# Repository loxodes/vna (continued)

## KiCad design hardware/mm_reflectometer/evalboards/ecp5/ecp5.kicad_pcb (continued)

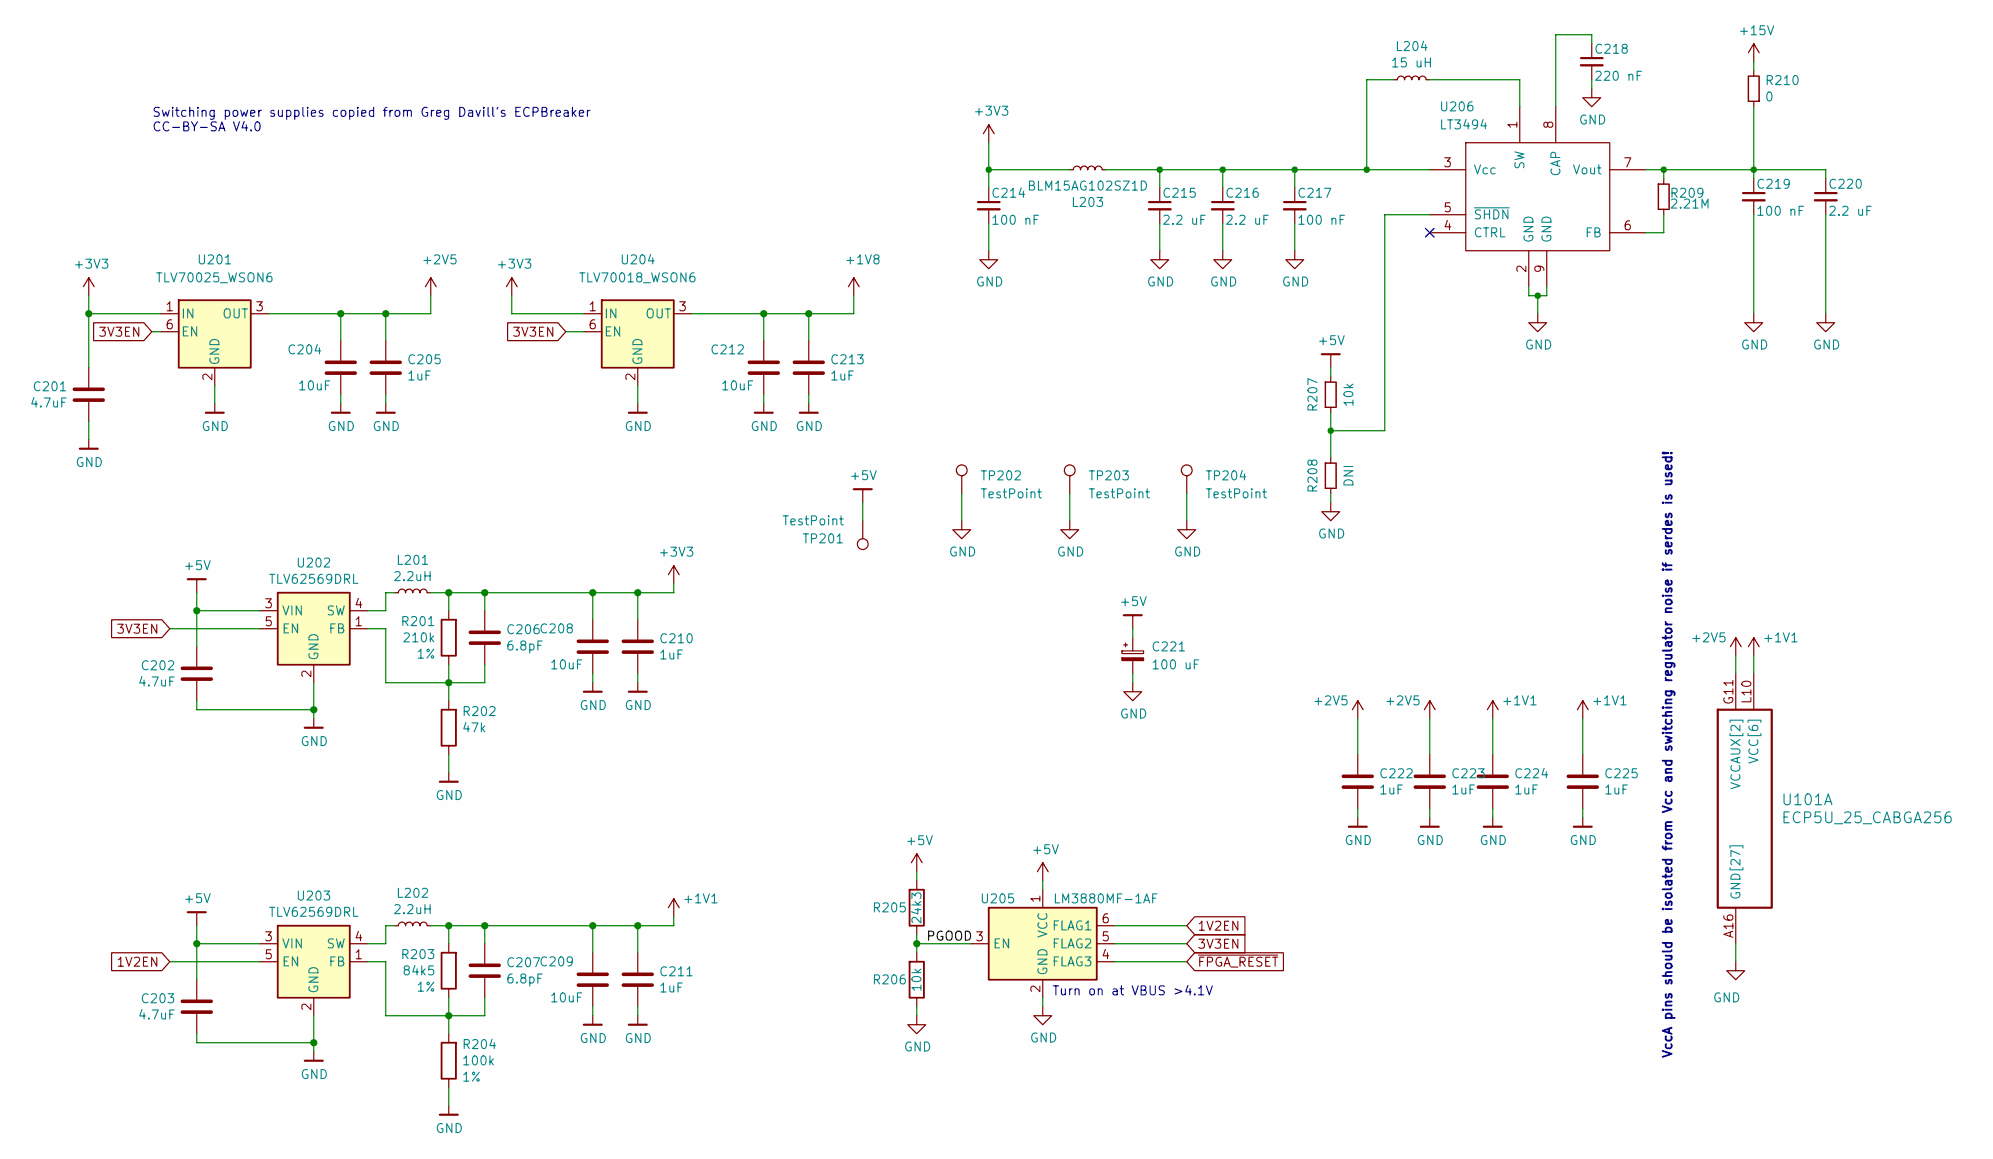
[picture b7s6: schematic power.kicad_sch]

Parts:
C201, C202, C203: 4.7uF; C_0402_1005Metric
C204, C208, C209, C212: 10uF; C_0603_1608Metric
C205, C210, C211, C213, C222, C223, C224, C225: 1uF; C_0402_1005Metric
C206, C207: 6.8pF; C_0402_1005Metric
C214, C217: 100 nF; C_0402_1005Metric
C215, C216, C220: 2.2 uF; C_0603_1608Metric
C218: 220 nF; C_0603_1608Metric
C219: 100 nF; C_0603_1608Metric
C221: 100 uF; CP_Elec_6.3x5.8
L201, L202: 2.2uH; L_0805_2012Metric
L203: BLM15AG102SZ1D; L_0402_1005Metric
L204: 15 uH; L_1210_3225Metric
R201: 210k; R_0402_1005Metric
R202: 47k; R_0402_1005Metric
R203: 84k5; R_0402_1005Metric
R204: 100k; R_0402_1005Metric
R205: 24k3; R_0402_1005Metric; MPN RC0402FR-1324K3L
R206: 10k; R_0402_1005Metric; MPN RC0402FR-1310KL
R207: 10k; R_0402_1005Metric
R208: DNI; R_0402_1005Metric
R209: 2.21M; R_0402_1005Metric
R210: 0; R_0603_1608Metric
TP201, TP202, TP203, TP204: TestPoint; TestPoint_Keystone_5015_Micro-Minature
U101: ECP5U_25_CABGA256; BGA-256_14.0x14.0mm_Layout16x16_P0.8mm_Ball0.45mm_Pad0.32mm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
U201: TLV70025_WSON6; WSON-6_1.5x1.5mm_P0.5mm
U202, U203: TLV62569DRL; SOT-666
U204: TLV70018_WSON6; WSON-6_1.5x1.5mm_P0.5mm
U205: LM3880MF-1AF; SOT-23-6; MPN LM3880MFX-1AF/NOPB
U206: LT3494; DFN-8-1EP_2x3mm_P0.5mm_EP0.61x2.2mm

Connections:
1V2EN: U203.5 (EN), U205.6 (FLAG1)
3V3EN: U201.6 (EN), U202.5 (EN), U204.6 (EN), U205.5 (FLAG2)
+1V1: C207.1, C209.1, C211.1, C224.1, C225.1, L202.2, R203.2, U101.G6 (VCC[6]), U101.G7 (VCC[6]), U101.G9 (VCC[6]), U101.L8 (VCC[6]), U101.L9 (VCC[6]), U101.L10 (VCC[6])
+1V8: C212.1, C213.1, U204.3 (OUT); also elsewhere on the board
+2V5: C204.1, C205.1, C222.1, C223.1, U101.G11 (VCCAUX[2]), U101.L7 (VCCAUX[2]), U201.3 (OUT)
+5V: C202.1, C203.1, C221.1, R205.2, R207.1, TP201.1, U202.3 (VIN), U203.3 (VIN), U205.1 (VCC); also elsewhere on the board
+15V: R210.2; also elsewhere on the board
/power/PGOOD: R205.1, R206.2, U205.3 (EN)
GND: C201.2, C202.2, C203.2, C204.2, C205.2, C208.2, C209.2, C210.2, C211.2, C212.2, C213.2, C214.2, C215.2, C216.2, C217.2, C218.2, C219.2, C220.2, C221.2, C222.2, C223.2, C224.2, C225.2, R202.1, R204.1, R206.1, R208.2, TP202.1, TP203.1, TP204.1, U101.A1 (GND[27]), U101.A16 (GND[27]), U101.D2 (GND[27]), U101.D15 (GND[27]), U101.F8 (GND[27]), U101.F9 (GND[27]), U101.G8 (GND[27]), U101.G10 (GND[27]), U101.H1 (GND[27]), U101.H8 (GND[27]), U101.H9 (GND[27]), U101.H10 (GND[27]), U101.H16 (GND[27]), U101.J8 (GND[27]), U101.J9 (GND[27]), U101.J10 (GND[27]), U101.K6 (GND[27]), U101.K7 (GND[27]), U101.K8 (GND[27]), U101.K9 (GND[27]), U101.K10 (GND[27]), U101.N2 (GND[27]), U101.N15 (GND[27]), U101.T1 (GND[27]), U101.T5 (GND[27]), U101.T12 (GND[27]), U101.T16 (GND[27]), U201.2 (GND), U202.2 (GND), U203.2 (GND), U204.2 (GND), U205.2 (GND), U206.2 (GND), U206.9 (GND); also elsewhere on the board
unnamed: C206.2, R201.1, R202.2, U202.1 (FB)
unnamed: C207.2, R203.1, R204.2, U203.1 (FB)
unnamed: C215.1, C216.1, C217.1, L203.1, L204.1, U206.3 (Vcc)
unnamed: C218.1, U206.8 (CAP)
unnamed: C219.1, C220.1, R209.1, R210.1, U206.7 (Vout)
unnamed: L201.1, U202.4 (SW)
unnamed: L202.1, U203.4 (SW)
unnamed: L204.2, U206.1 (SW)
unnamed: R207.2, R208.1, U206.5 (~SHDN)
unnamed: R209.2, U206.6 (FB)
~FPGA_RESET: U205.4 (FLAG3); also elsewhere on the board

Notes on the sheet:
Switching power supplies copied from Greg Davill's ECPBreaker CC-BY-SA V4.0
Turn on at VBUS >4.1V
VccA pins should be isolated from Vcc and switching regulator noise if serdes is used!

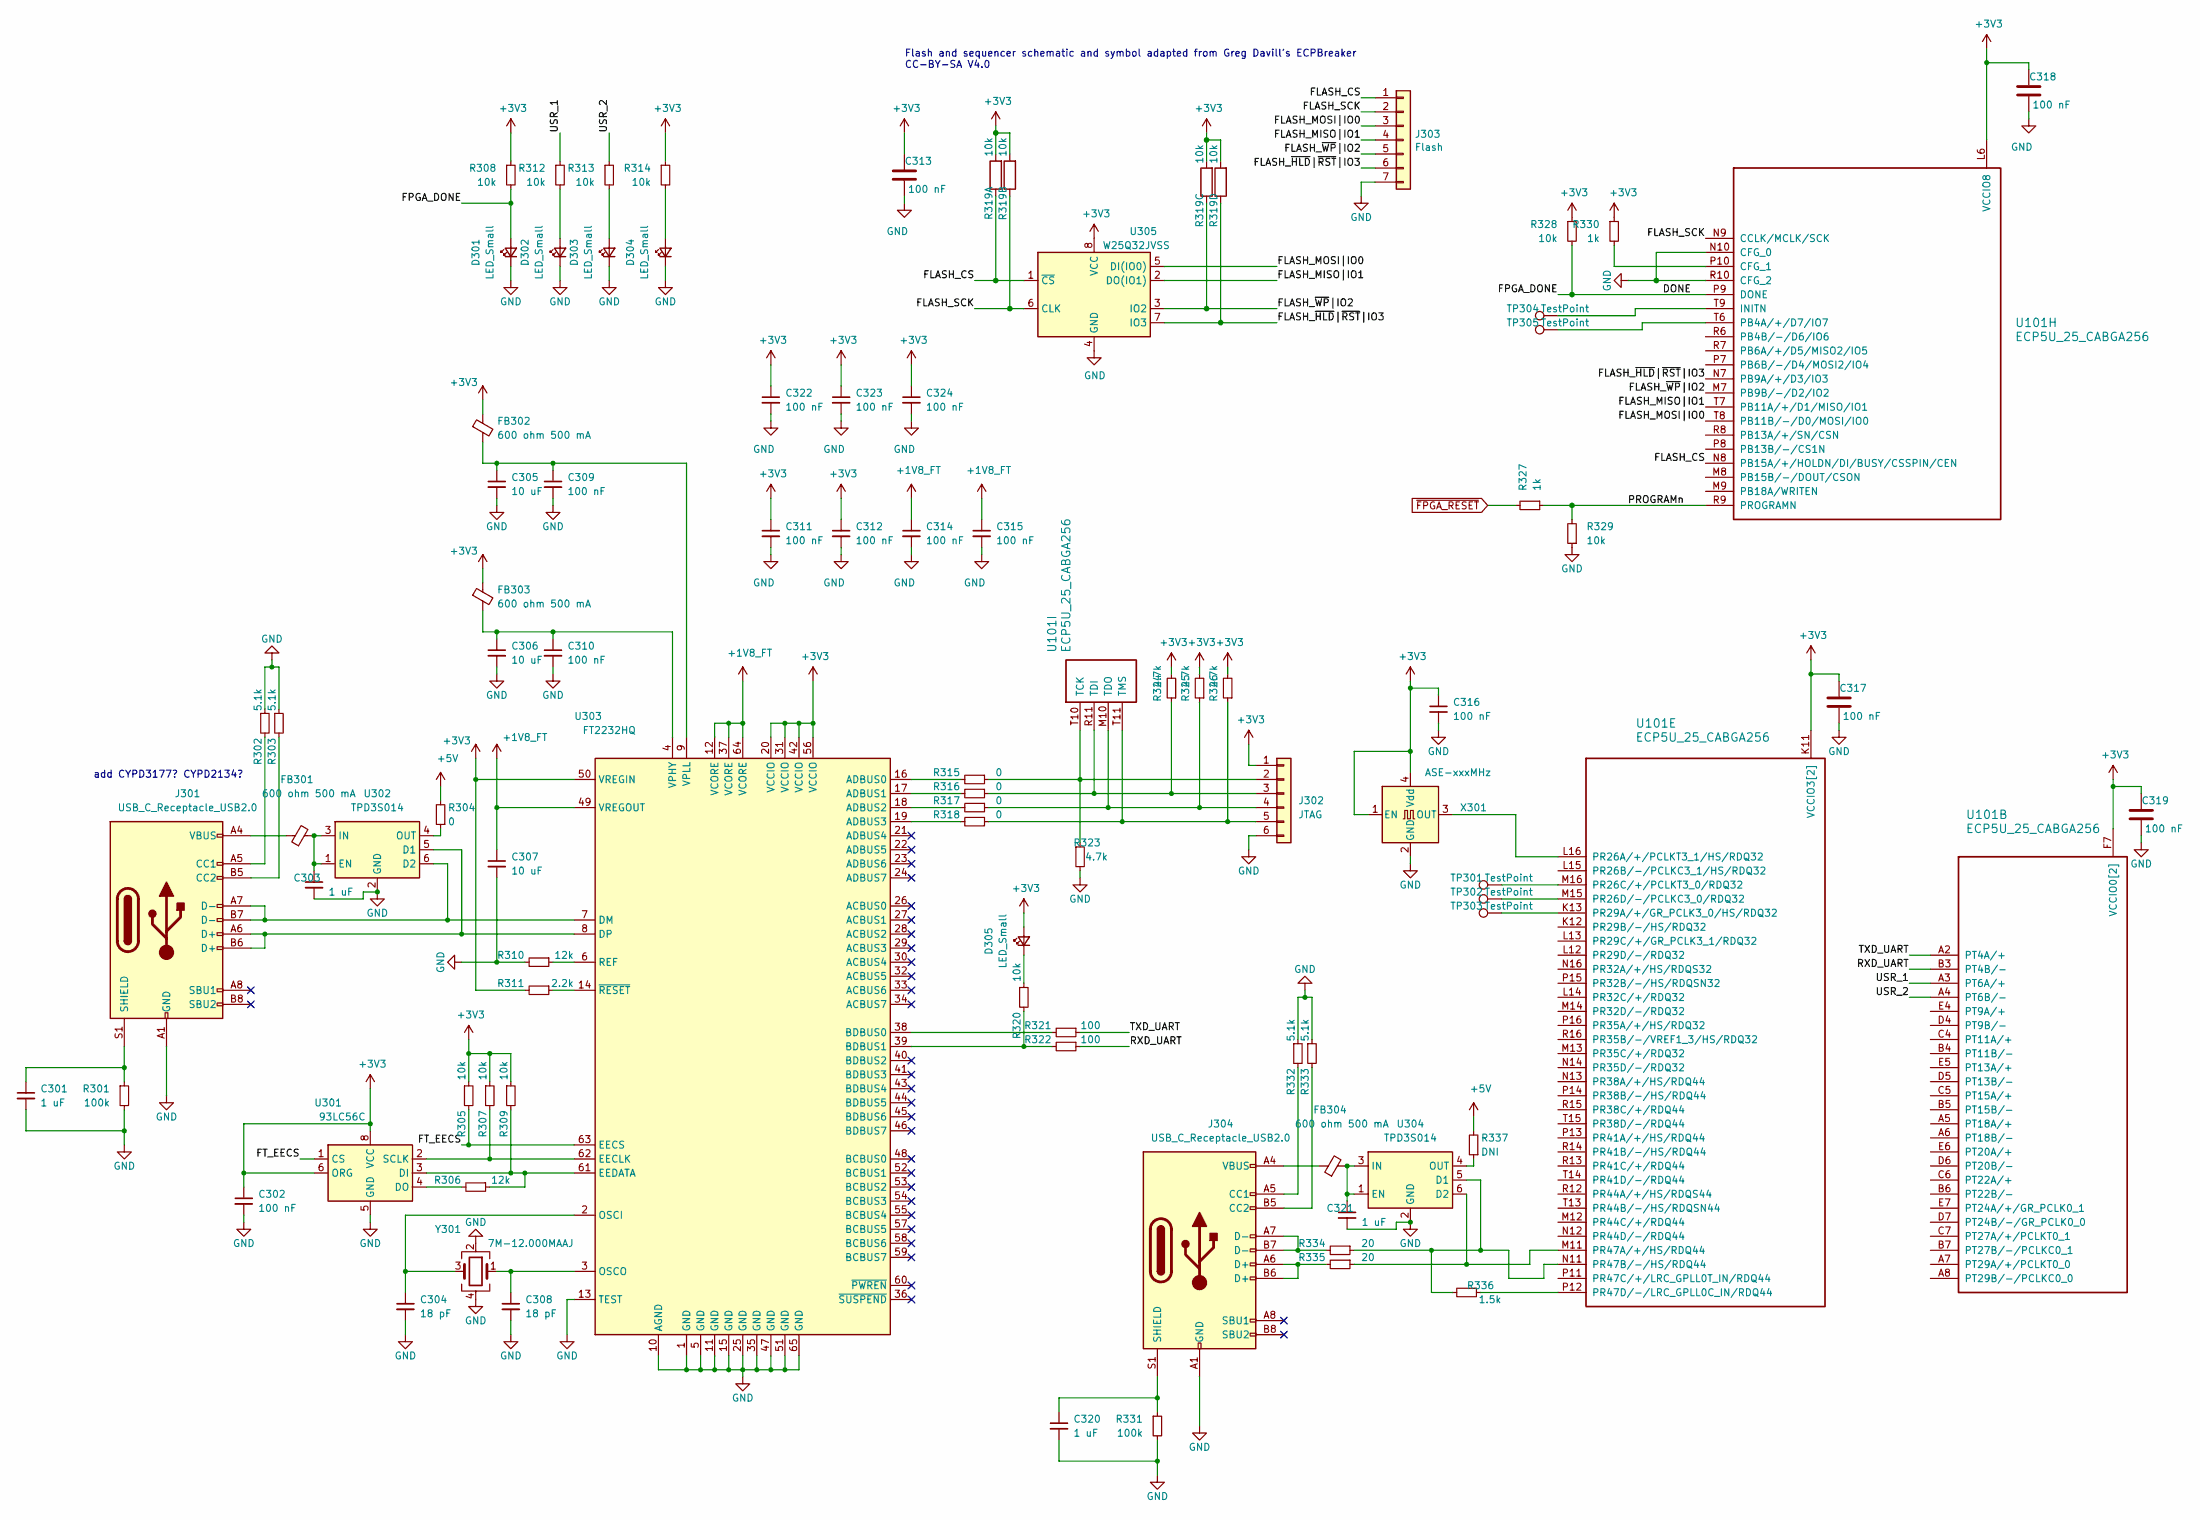
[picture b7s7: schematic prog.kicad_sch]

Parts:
C301, C303, C320, C321: 1 uF; C_0402_1005Metric
C302, C309, C310, C311, C312, C313, C314, C315, C316, C317, C318, C319, C322, C323, C324: 100 nF; C_0402_1005Metric
C304, C308: 18 pF; C_0402_1005Metric
C305, C306, C307: 10 uF; C_0603_1608Metric
D301, D302, D303, D304, D305: LED_Small; LED_0603_1608Metric
FB301, FB302, FB303, FB304: 600 ohm 500 mA; L_0603_1608Metric
J301, J304: USB_C_Receptacle_USB2.0; USB_C_Receptacle_HRO_TYPE-C-31-M-12
J302: JTAG; PinHeader_1x06_P2.54mm_Vertical
J303: Flash; PinHeader_1x07_P2.54mm_Vertical
R301, R331: 100k; R_0402_1005Metric
R302, R303, R332, R333: 5.1k; R_0402_1005Metric
R304, R315, R316, R317, R318: 0; R_0402_1005Metric
R305, R307, R308, R309, R312, R313, R314, R320, R328, R329: 10k; R_0402_1005Metric
R306, R310: 12k; R_0402_1005Metric
R311: 2.2k; R_0402_1005Metric
R319: 10k; R_Array_Convex_4x0402
R321, R322: 100; R_0402_1005Metric
R323, R324, R325, R326: 4.7k; R_0402_1005Metric
R327, R330: 1k; R_0402_1005Metric
R334, R335: 20; R_0402_1005Metric
R336: 1.5k; R_0402_1005Metric
R337: DNI; R_0402_1005Metric
TP301, TP302, TP303, TP304, TP305: TestPoint; TestPoint_Pad_D1.5mm
U101: ECP5U_25_CABGA256; BGA-256_14.0x14.0mm_Layout16x16_P0.8mm_Ball0.45mm_Pad0.32mm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
U301: 93LC56C; SOIC-8_5.23x5.23mm_P1.27mm
U302, U304: TPD3S014; SOT-23-6
U303: FT2232HQ; QFN-64-1EP_9x9mm_P0.5mm_EP4.35x4.35mm
U305: W25Q32JVSS; WSON-8-1EP_6x5mm_P1.27mm_EP3.4x4mm
X301: ASE-xxxMHz; Oscillator_SMD_Abracon_ASE-4Pin_3.2x2.5mm
Y301: 7M-12.000MAAJ; Crystal_SMD_3225-4Pin_3.2x2.5mm

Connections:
+1V8_FT: C307.1, C314.1, C315.1, U303.12 (VCORE), U303.37 (VCORE), U303.49 (VREGOUT), U303.64 (VCORE)
+5V: R304.2, R337.2; also elsewhere on the board
/prog/DONE: D301.2 (A), R308.2, R328.2, U101.P9 (DONE)
/prog/FLASH_CS: J303.1, R319.8, U101.N8 (PB15A/+/HOLDN/DI/BUSY/CSSPIN/CEN), U305.1 (~CS)
/prog/FLASH_MISO|IO1: J303.4, U101.T7 (PB11A/+/D1/MISO/IO1), U305.2 (DO(IO1))
/prog/FLASH_MOSI|IO0: J303.3, U101.T8 (PB11B/-/D0/MOSI/IO0), U305.5 (DI(IO0))
/prog/FLASH_SCK: J303.2, R319.7, U101.N9 (CCLK/MCLK/SCK), U305.6 (CLK)
/prog/FLASH_~HLD~|~RST~|IO3: J303.6, R319.5, U101.N7 (PB9A/+/D3/IO3), U305.7 (IO3)
/prog/FLASH_~WP~|IO2: J303.5, R319.6, U101.M7 (PB9B/-/D2/IO2), U305.3 (IO2)
/prog/FT_EECS: R305.2, U301.1 (CS), U303.63 (EECS)
/prog/PROGRAMn: R327.1, R329.2, U101.R9 (PROGRAMN)
/prog/RXD_UART: R322.1, U101.B3 (PT4B/-)
/prog/TXD_UART: R321.1, U101.A2 (PT4A/+)
/prog/USR_1: R312.1, U101.A3 (PT6A/+)
/prog/USR_2: R313.1, U101.A4 (PT6B/-)
GND: C301.2, C302.2, C303.2, C304.2, C305.2, C306.2, C307.2, C308.2, C309.2, C310.2, C311.2, C312.2, C313.2, C314.2, C315.2, C316.2, C317.2, C318.2, C319.2, C320.2, C321.2, C322.2, C323.2, C324.2, D301.1 (K), D302.1 (K), D303.1 (K), D304.1 (K), J301.A1 (GND), J301.A12 (GND), J301.B1 (GND), J301.B12 (GND), J302.6, J303.7, J304.A1 (GND), J304.A12 (GND), J304.B1 (GND), J304.B12 (GND), R301.2, R302.1, R303.1, R310.2, R323.2, R329.1, R331.2, R332.1, R333.1, U101.N10 (CFG_0), U101.R10 (CFG_2), U301.5 (GND), U302.2 (GND), U303.1 (GND), U303.5 (GND), U303.10 (AGND), U303.11 (GND), U303.13 (TEST), U303.15 (GND), U303.25 (GND), U303.35 (GND), U303.47 (GND), U303.51 (GND), U303.65 (GND), U304.2 (GND), U305.4 (GND), X301.2 (GND), Y301.2, Y301.4; also elsewhere on the board
unnamed: C301.1, J301.S1 (SHIELD), R301.1
unnamed: C303.1, FB301.2, U302.1 (EN), U302.3 (IN)
unnamed: C304.1, U303.2 (OSCI), Y301.3
unnamed: C305.1, C309.1, FB302.2, U303.9 (VPLL)
unnamed: C306.1, C310.1, FB303.2, U303.4 (VPHY)
unnamed: C308.1, U303.3 (OSCO), Y301.1
unnamed: C320.1, J304.S1 (SHIELD), R331.1
unnamed: C321.1, FB304.2, U304.1 (EN), U304.3 (IN)
unnamed: D302.2 (A), R312.2
unnamed: D303.2 (A), R313.2
unnamed: D304.2 (A), R314.2
unnamed: D305.1 (K), R320.1
unnamed: FB301.1, J301.A4 (VBUS), J301.A9 (VBUS), J301.B4 (VBUS), J301.B9 (VBUS)
unnamed: FB304.1, J304.A4 (VBUS), J304.A9 (VBUS), J304.B4 (VBUS), J304.B9 (VBUS)
unnamed: J301.A5 (CC1), R302.2
unnamed: J301.A6 (D+), J301.B6 (D+), U302.5 (D1), U303.8 (DP)
unnamed: J301.A7 (D-), J301.B7 (D-), U302.6 (D2), U303.7 (DM)
unnamed: J301.B5 (CC2), R303.2
unnamed: J302.2, R315.1, R323.1, U101.T10 (TCK)
unnamed: J302.3, R316.1, R324.1, U101.R11 (TDI)
unnamed: J302.4, R317.1, R325.1, U101.M10 (TDO)
unnamed: J302.5, R318.1, R326.1, U101.T11 (TMS)
unnamed: J304.A5 (CC1), R332.2
unnamed: J304.A6 (D+), J304.B6 (D+), R335.2
unnamed: J304.A7 (D-), J304.B7 (D-), R334.2
unnamed: J304.B5 (CC2), R333.2
unnamed: R304.1, U302.4 (OUT)
unnamed: R306.1, R309.2, U301.3 (DI), U303.61 (EEDATA)
unnamed: R306.2, U301.4 (DO)
unnamed: R307.2, U301.2 (SCLK), U303.62 (EECLK)
unnamed: R310.1, U303.6 (REF)
unnamed: R311.1, U303.14 (~RESET)
unnamed: R315.2, U303.16 (ADBUS0)
unnamed: R316.2, U303.17 (ADBUS1)
unnamed: R317.2, U303.18 (ADBUS2)
unnamed: R318.2, U303.19 (ADBUS3)
unnamed: R320.2, R322.2, U303.39 (BDBUS1)
unnamed: R321.2, U303.38 (BDBUS0)
unnamed: R330.2, U101.P10 (CFG_1)
unnamed: R334.1, R336.2, U101.N11 (PR47B/-/HS/RDQ44), U304.5 (D1)
unnamed: R335.1, U101.M11 (PR47A/+/HS/RDQ44), U304.6 (D2)
unnamed: R336.1, U101.P12 (PR47D/-/LRC_GPLL0C_IN/RDQ44)
unnamed: R337.1, U304.4 (OUT)
unnamed: TP301.1, U101.M16 (PR26C/+/PCLKT3_0/RDQ32)
unnamed: TP302.1, U101.M15 (PR26D/-/PCLKC3_0/RDQ32)
unnamed: TP303.1, U101.K13 (PR29A/+/GR_PCLK3_0/HS/RDQ32)
unnamed: TP304.1, U101.T9 (INITN)
unnamed: TP305.1, U101.T6 (PB4A/+/D7/IO7)
unnamed: U101.L16 (PR26A/+/PCLKT3_1/HS/RDQ32), X301.3 (OUT)
~FPGA_RESET: R327.2; also elsewhere on the board

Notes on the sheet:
add CYPD3177? CYPD2134?
Flash and sequencer schematic and symbol adapted from Greg Davill's ECPBreaker CC-BY-SA V4.0

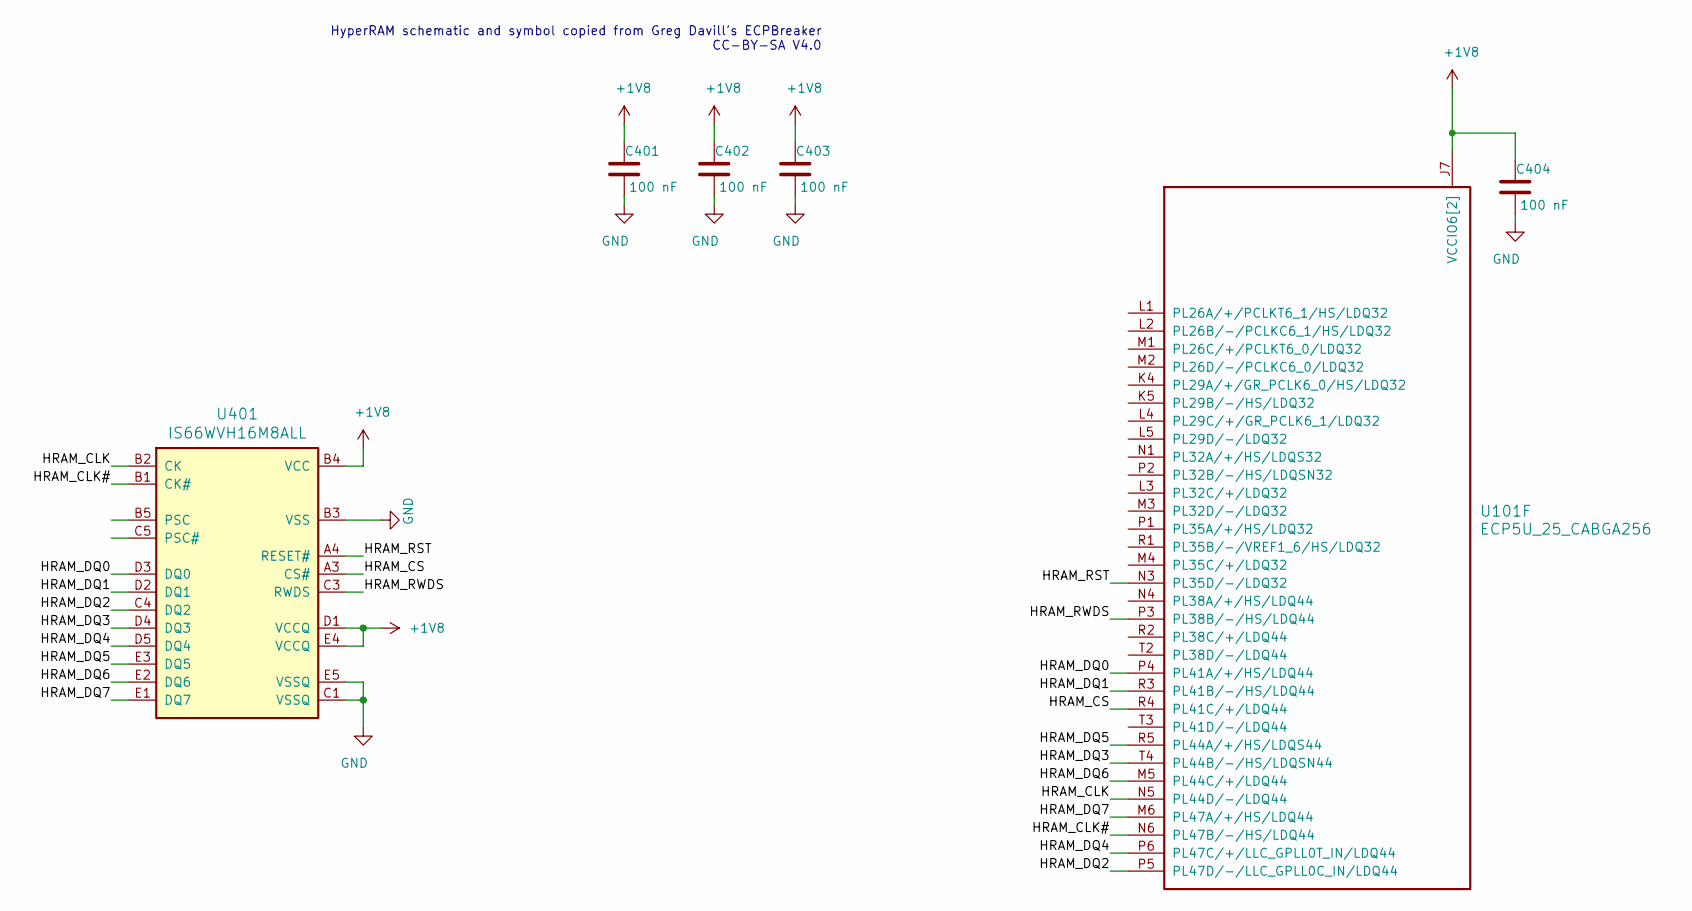
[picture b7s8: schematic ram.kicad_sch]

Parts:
C401, C402, C403, C404: 100 nF; C_0402_1005Metric
U101: ECP5U_25_CABGA256; BGA-256_14.0x14.0mm_Layout16x16_P0.8mm_Ball0.45mm_Pad0.32mm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
U401: IS66WVH16M8ALL; BGA-24_8.0x6.0mm_Layout5x5_P0.8mm_Pad0.35mm_NSMD

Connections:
+1V8: C401.1, C402.1, C403.1, C404.1, U101.J6 (VCCIO6[2]), U101.J7 (VCCIO6[2]), U401.B4 (VCC), U401.D1 (VCCQ), U401.E4 (VCCQ); also elsewhere on the board
/ram/HRAM_CLK: U101.N5 (PL44D/-/LDQ44), U401.B2 (CK)
/ram/HRAM_CLK#: U101.N6 (PL47B/-/HS/LDQ44), U401.B1 (CK#)
/ram/HRAM_CS: U101.R4 (PL41C/+/LDQ44), U401.A3 (CS#)
/ram/HRAM_DQ0: U101.P4 (PL41A/+/HS/LDQ44), U401.D3 (DQ0)
/ram/HRAM_DQ1: U101.R3 (PL41B/-/HS/LDQ44), U401.D2 (DQ1)
/ram/HRAM_DQ2: U101.P5 (PL47D/-/LLC_GPLL0C_IN/LDQ44), U401.C4 (DQ2)
/ram/HRAM_DQ3: U101.T4 (PL44B/-/HS/LDQSN44), U401.D4 (DQ3)
/ram/HRAM_DQ4: U101.P6 (PL47C/+/LLC_GPLL0T_IN/LDQ44), U401.D5 (DQ4)
/ram/HRAM_DQ5: U101.R5 (PL44A/+/HS/LDQS44), U401.E3 (DQ5)
/ram/HRAM_DQ6: U101.M5 (PL44C/+/LDQ44), U401.E2 (DQ6)
/ram/HRAM_DQ7: U101.M6 (PL47A/+/HS/LDQ44), U401.E1 (DQ7)
/ram/HRAM_RST: U101.N3 (PL35D/-/LDQ32), U401.A4 (RESET#)
/ram/HRAM_RWDS: U101.P3 (PL38B/-/HS/LDQ44), U401.C3 (RWDS)
GND: C401.2, C402.2, C403.2, C404.2, U401.B3 (VSS), U401.C1 (VSSQ), U401.E5 (VSSQ); also elsewhere on the board

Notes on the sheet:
HyperRAM schematic and symbol copied from Greg Davill's ECPBreaker CC-BY-SA V4.0

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
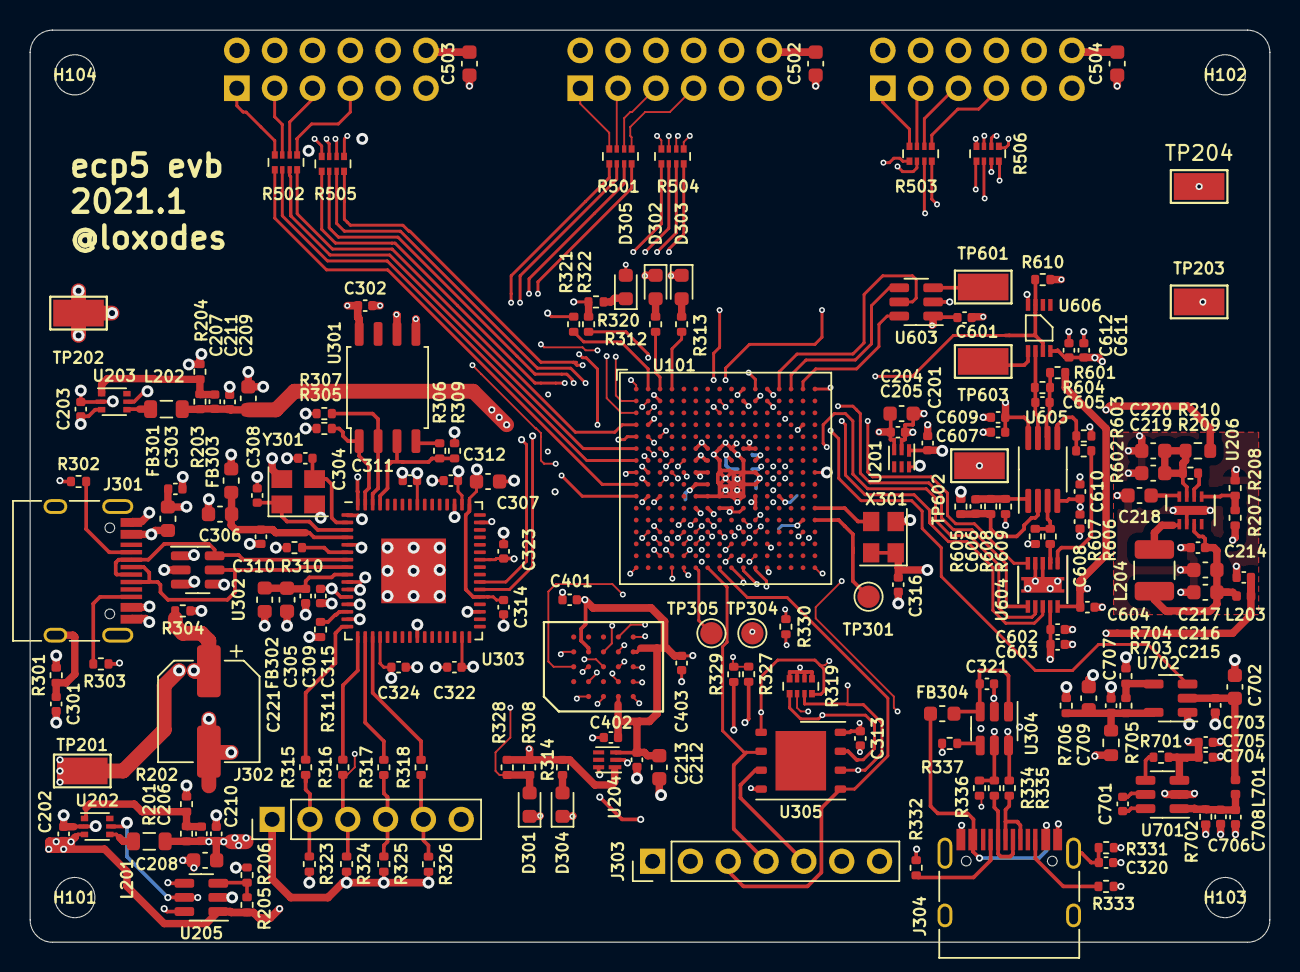
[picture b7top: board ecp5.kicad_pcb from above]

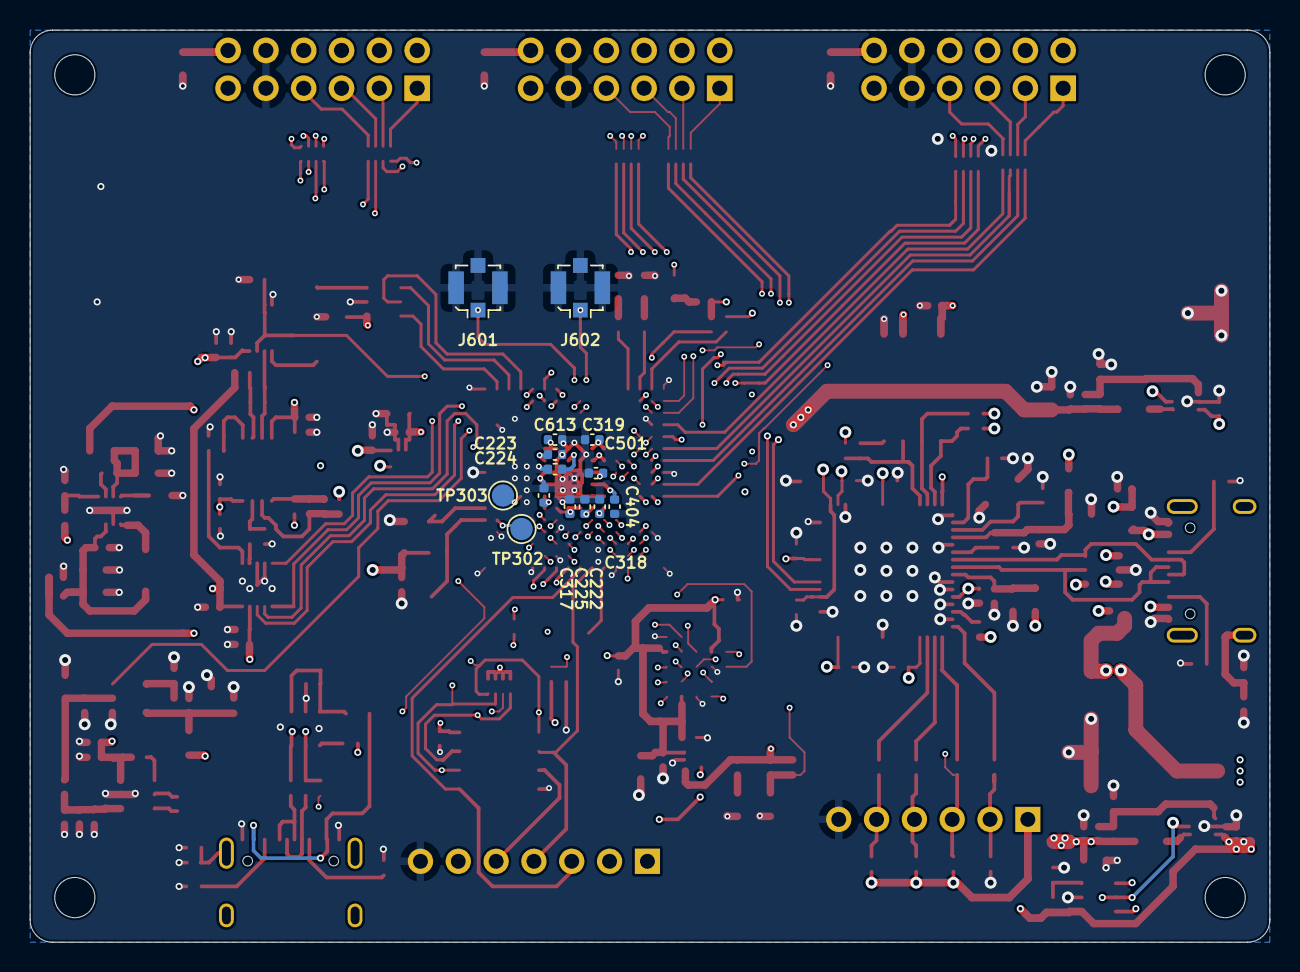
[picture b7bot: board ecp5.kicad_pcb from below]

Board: 6 copper layers, 83.2 x 61.2 mm, 208 parts (14 on the bottom side), 176 nets.

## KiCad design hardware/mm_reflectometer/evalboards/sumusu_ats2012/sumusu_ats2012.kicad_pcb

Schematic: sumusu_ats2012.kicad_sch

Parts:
AT1: ATS2012; mpn ATS2012-xxdB-XX
J1, J2: Conn_Coaxial; sw_edge_oshpark_4layer

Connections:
GND: AT1.3, J1.2 (Ext), J2.2 (Ext)
unnamed: AT1.1, J1.1 (In)
unnamed: AT1.2, J2.1 (In)

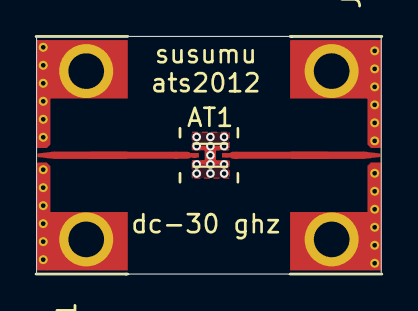
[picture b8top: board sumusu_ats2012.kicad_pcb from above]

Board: 4 copper layers, 19.2 x 13.2 mm, 3 parts (0 on the bottom side), 3 nets.

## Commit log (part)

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2016-09-28 added values to ad9864 lo pll, added missing pullup resistors, work on ad9864 test sketch
2016-09-30 started on OSD3358 based control board
2016-10-02 calculated ad9864 register values for 45 MHz IF, 26 MHz fclk
2016-10-03 actually applied bugfix for ad9864 spi..
2016-10-04 fixed clk on ad9864, registers now set to use external XCO for fclk..
2016-10-08 ad9864 board working w/ 45 MHz IF
2016-10-09 ad9864 sample streaming into beaglebone pru shared memory swing buffer working
2016-10-09 streaming samples over sockets to python works, adding beaglebone code
2016-10-11 added sweep for hmc311 cpw amplifier
    (the maam-01101 didn't work as well.. ~2 dB of gain)
2016-10-12 modified mixer breakout to work with ltc5548, moved to soldermask defined pads
2016-10-12 switched switch board to be coplanar waveguide fed
2016-10-21 ordered pe42540 breakout
2016-10-21 work on controller board - ethernet and microsd schematic
2016-10-22 work on USB schematic for controller
2016-10-24 silkscreen cleanup on demod board
2016-10-24 added gerber files for r0 demod board
2016-10-25 started clk/lo buffer for demod boards
2016-10-26 started on control cape for 4 receiver vna
2016-10-27 routed adc/synth cape
2016-10-28 started working on vna control software for non-zero IF and separate RF/LO synths
2016-10-28 .. actually added script to initalize ad9864
2016-10-29 fixed bugs in beaglebone ad9864 init script..
2016-10-29 sweeping with 45 MHz IF VNA..
2016-10-31 work on vna driver software..
2016-10-31 actually added pru changes
2016-10-31 increased sweep speed
2016-11-01 started on support for non-ideal cal kits
2016-11-06 fixed footprints for filters on synth board
2016-11-10 work on next revision synth
2016-11-13 updated readme a little
2016-11-14 removed abandoned breakout boards/modules
2016-11-15 started on beaglebone port of lmx2592 driver
2016-11-20 added missing bit-banged SPI driver..
2016-11-21 move adc over to pru1
2016-11-21 .. actually added synth changes
2016-11-23 mixer on demod board now working
2016-11-27 more work on vna beaglebone control..
2016-11-29 add ltc rf detector symbol
2016-11-29 fixed some syntax errors on beaglebone zmq io servers
2016-11-29 fixed typos in pin definitions for beaglebone control..
2016-11-30 beaglebone gpio server now working
2016-11-30 synth server now working
2016-12-03 enabled adc channels 2-4 on pru..
2016-12-04 added divider to output of clock buffer to avoid overloading adc fref...
2016-12-05 adc simultaneous sampling now working..
2016-12-07 set SYNCB high after adc init in io server, added tristate mosi command, work on two port calibration
2016-12-11 fixed synth output between 3.55 GHz and 7.1 GHz..
2016-12-12 added some pictures of the VNA
2016-12-14 draw block diagram of current prototype
2017-02-01 fixed i/q swap in ad9864 samples
2017-02-06 reduce sweep time by starting both rf and lo frequency tune commands before waiting for pll locks
2017-02-09 added cal table to level vna output power to -10 dBm
2017-02-21 continuously update rf/lo synth offset across sweeps
2017-03-31 added script for processing raw s2p files
2017-04-03 started libs for next hardware revision, more s2p processing scripts..
2017-04-28 added some pictures
2017-05-14 added SMA footprints for cpw edge launch
2017-06-08 added lmx2594 symbol
2017-06-12 work on vna r0 schematics
2017-06-13 finiished schematic for vna r0 rf board
2017-06-14 added footprints for filters
2017-06-19 started component placement on demod
2017-06-19 work on vna r0 component placement
2017-06-22 work on demod layout
2017-06-24 work on vna r0 layout
2017-06-26 routing on demod, almost done..
2017-06-27 routing vna rf r0
2017-06-29 finished vna rf r0 layout
2017-06-29 removed unnecessary dc blocking caps on demod synth
2017-06-30 final cleanup of vna r0 pcbs, ordered boards
2017-07-05 started layout of vna r0 control cape
2017-07-07 layout of control cape..
2017-07-08 finished vna control cape
2017-07-09 added BOMs for vna r0 boards
2017-07-10 started porting sofware to next revision synth, wrote ad9577 driver
2017-07-16 added script for converting TICS pro register dumps to python dictionaries
2017-07-20 added control of macom vga in rf synth board
2017-07-31 don't enable PDRefOut on ad9577, fix synth ref clock calculation
2017-08-02 fixed filter bank path selection for frequencies below 2.5 GHz, vna r0 rf board appears to work
2017-08-04 work on lxm2594 driver..
2017-08-06 lmx2594 synth driver and vna_rf board appear to work! (except vga.., still working on that..)
2017-08-06 fixed feedback network on vga vctrl op amp
2017-08-10 added some block diagrams and comments
2017-08-10 fixed markdown syntax?
2017-08-18 changes to vna client code for r0
2017-08-18 bugfixes to vna driver code for vna r0
2017-08-22 added output power leveling for vna r0
2017-08-22 beaglebone side bugfixes to output power leveling
2017-08-26 added collection of switch terms for improved two port calibration
2017-08-28 two port calibration working!
2017-09-01 fixed sweep collection for LMR16, tested LMR16 cal
2017-09-10 added TRL calibration boards for oshpark 4 layer microstrip and amphenol 901-10512-3 connectors
2017-09-24 started on single PCB version of vna
2017-09-26 work on vna r1 schematic - ethernet
2017-09-30 started on macom maam-011100 vga module
2017-10-02 work on control lines for vna r1..
2017-11-02 fix README formatting
2017-11-04 added support for calibration standards defined by fringing capacitance coefficients
2017-11-06 added support for processing data with trl calibration
2017-11-17 started on resistive bridge coupler test board
2017-11-17 cleanup of resistive bridge layout
2018-03-04 component placement on vna r1
2018-03-11 layout on vna r1 control board
2018-03-22 more work on vna r1..
2018-04-02 added passive component test boards, revised coupler
2018-04-05 work on vna r1 demod schematic
2018-04-09 added footprint for PAT0510S attenuators
2018-04-12 added sot89 amplifier breakout
2018-04-14 started layout on vna r1 synth and demod..
2018-04-14 added notes on coupler setup
2018-04-16 work on demod - added fixed attenuator to ref path, fixed bridge symbol and footprint
2018-04-19 component placement on vna r1 demod and synth
2018-04-21 added measured data on adrf5020 breakout, it works
2018-04-23 layout of vna r1 control board
2018-05-05 component placement on adcs
2018-05-05 vna r1 control layout..
2018-05-06 all nets connected on vna r1 control board..
2018-05-07 finished vna r1 control, ordered pcbs
2018-05-11 layout on vna r1 demod
2018-05-13 all nets connected on vna synth r1
2018-05-14 do not have paste layer for TP-P20B test points
2018-05-20 added pos files and board images for meatbagpnp hand assembly
2018-06-22 add BOMs for vna r1 boards
2018-07-01 added missing demod schematics
2018-07-15 started porting over control software to vna r1
2018-07-27 fix MAAM-011100 bias voltage divider and LD39100PUR regulator adjust circuit on vna_r1_synth. thanks Santiago!
2018-08-02 started vna r1 device tree overlay
2018-08-26 fix author
2018-08-30 fix gpio0 base address, enable gpio clks
2018-09-03 update PRU ADC DTS for VNA r1
2018-09-08 rewrote adc_client to work with new remoteproc adc_to_socket program
2018-09-08 added picture of vna r1 control board
2018-09-13 ported zmq io server to new gpio driver
2018-09-20 set SYNCB as output in zmq_io_server...
2018-09-23 updated vna_driver.py for vna r1 - added io client support for switchable attenuation
2018-10-22 bypass if filter in vna r1 demod
2018-10-25 added (untested) footprint for SF2921-61345 sma connector
2019-08-02 started maam-011109 breakout
2019-08-02 finished maam-011109 breakout layout
2019-08-25 added maam-011109 Vc bias board
2019-09-01 added power supply sequencing
2019-09-04 finished sequencing circuit breakout schematic
2019-09-06 work on sequencing layout
2019-09-07 layout on sequencer, fix QFN28 paste mask
2019-09-08 silkscreen cleanup, ordered sequencing test boards
2019-09-09 add values for feedback resistors on power sequencing test board
2019-09-13 changed synth midband filter bank to admv8416, added rf test points
2019-09-21 added vias to siw footprint generator
2019-10-01 added values for divider resistors for negative voltage monitoring, generated interactive BOMs for maam-011109 bias and sequencing breakout boards
2019-10-20 started variable filter bias circuitry - added 15V bias
2019-10-27 cleaned up old hardware revisions
2019-10-28 work on reference board
2019-10-29 added regulator to vna mm ref board
2019-11-06 added input overvoltage, undervoltage, and reverse polarity protection
2019-11-07 added protection to digital inputs
2019-11-10 component placement on vna ref board
2019-11-12 work on layout of vna mm ref board
2019-11-13 silkscreen cleanup
2019-11-15 created BOM for vna mm ref
2019-11-23 added schematic export and picture of assembled board
2019-12-05 cleanup and update vna mm synth schematic for modern kicad libraries
2019-12-06 footprint assignment
2019-12-08 added power input protection, footprint assignment on synth
2019-12-13 cleanup synth footprint paste mask, added adc for sampling vdet
2019-12-18 work on mm synth io lines
2019-12-21 work on vna mm synth digital lines, added i2c eeprom
2019-12-22 added pulldowns to digital inputs on vna mm synth
2019-12-28 started component placement on vna mm synth
2020-02-06 started litex soc on ecp5 versa for adc344x adc testing
2020-02-18 added dac7563 driver to soc
2020-04-20 create hyperram -> ECP5 versa breakout
2020-04-24 finished first pass adc32xx schematic
2020-05-04 finished layout of adc32xx ecp5 board
2020-05-10 added litex core with support for hyperram breakout
2020-06-04 fifo streaming to hyperram kinda works
2020-06-07 hyperram still breaks writing across page boundaries, last commit before switching to hyperramx2
2020-06-29 spi writing to initialize the ADC works
2020-07-07 commit before fixing dout1/dx0/dx1 interleaving of adc3222 output
2020-07-09 adc3222 writing to hyperram ... kinda works, samples sometimes repeated with sine wave test pattern
2020-07-11 save ADC samples to sram, still skipping writes..
2020-07-13 added adt2-1t balun breakout
2020-07-19 added plotting of spectrum magnitude from adc, updated makefiles/linker to work with current litex, increased wb serial bridge baud rate to 3 mbaud
2020-08-10 added libraries for phase noise analyzer
2020-12-25 layout of sumusu ats eval board
2020-12-29 created eval boards for parts on ~8-30 GHz vector reflectometer
2021-01-03 routing on ecp5 eval board
2021-01-03 silkscreen cleanup, board passes DRC
2021-01-24 fixed maam-011101 eval board pinout, started bringup of ecp5 board
2021-01-25 added support for hyperram and programming to flash to litex soc
2021-03-14 add assembly drawing for maam-011132, change active bias op-amp to TLV9151
2021-03-22 added xx1000-qt breakout board
2021-04-04 added dac to mm_synth for vtune/adjstable bias, added ADC for telemetry
2021-04-04 started digital control schematic page on mm_synth, removed stale documentation
2021-04-24 added pcb assembly drawing for xx1000-qt module
2021-05-27 library updates
2021-08-22 work on mm synth schematic - control signals and footprint assignments
2021-08-23 schematic cleanup, erc
2021-09-07 created HUSB238 eval board, added clock splitter to mm synth
2021-09-25 added missing synth files
2021-09-26 commit mm_synth prior to updating from june to september kicad-nightly build
2021-10-02 component placement on mm synth
2022-03-06 component placement
2022-06-12 started fpga-less synthesizer module
2023-11-19 bias controller schematic work
2023-11-25 more bias controller schematic work
2023-11-27 finished first pass at bias controller schematic
2023-12-03 most footprint assignments on bias controller board, schematic cleanup
2023-12-18 added board to board connector
